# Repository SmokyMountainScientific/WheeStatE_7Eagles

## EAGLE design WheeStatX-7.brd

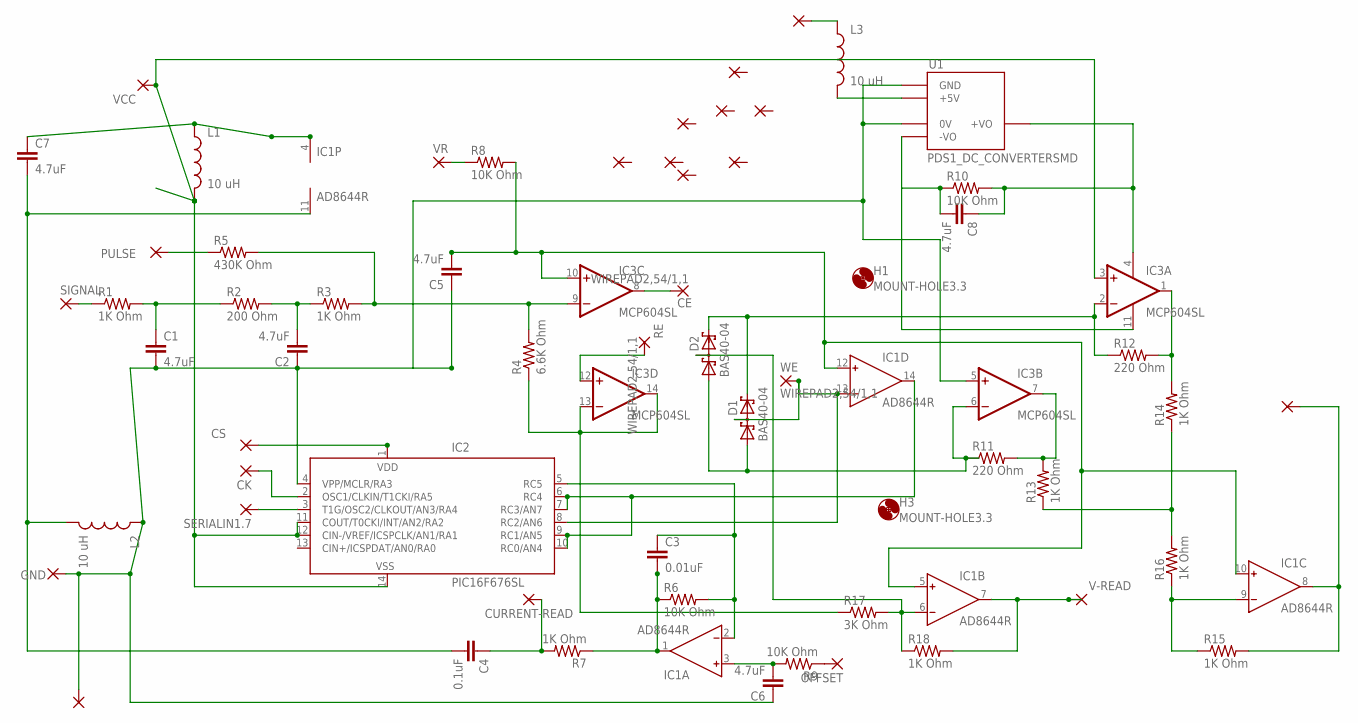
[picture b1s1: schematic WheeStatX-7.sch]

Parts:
1, 1.1, 1.4, 2, 3, 4, 5, 6, 7, 9, 10: 1,6/0,9
C1, C2, C5, C6, C8: 4.7uF; C0603
C3: 0.01uF; C0603
C4: 0.1uF; C0603
C7: 4.7uF; C0603@1
CE: WIREPAD2,54/1,1; 2,54/1,1
CK: 1,6/0,9
CS: 1,6/0,9
CURRENT-READ: 1,6/0,9
D1, D2: BAS40-04; SOT23
GND: 1,6/0,9
H1, H3: MOUNT-HOLE3.3; 3,3
IC1: AD8644R; SO14
IC2: PIC16F676SL; SO-14
IC3: MCP604SL; SO14
L1, L2, L3: 10 uH; 0603
OFFSET: 1,6/0,9
PULSE: 1,6/0,9
R1, R3, R7, R13, R14, R15, R16, R18: 1K Ohm; R0603
R2: 200 Ohm; R0603
R4: 6.6K Ohm; R0603
R5: 430K Ohm; R0603
R6, R8, R9, R10: 10K Ohm; R0603
R11, R12: 220 Ohm; R0603
R17: 3K Ohm; R0603
RE: WIREPAD2,54/1,1; 2,54/1,1
SERIALIN1.7: 1,6/0,9
SIGNAL: 1,6/0,9
U1: PDS1_DC_CONVERTERSMD; PDS1
V-READ: 1,6/0,9
VCC: 1,6/0,9
VR: 1,6/0,9
WE: WIREPAD2,54/1,1; 2,54/1,1

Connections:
GND: 1.1.1, C1.2, C2.1, C5.1, C6.1, GND.1, IC2.4 (VPP/MCLR/RA3), IC3.5 (+IN), L2.1, U1.1 (GND), U1.4 (0V)
unnamed: IC1.9 (IN-), R15.1, R16.1
unnamed: IC3.13 (-IN), IC3.14 (OUT), R4.1, R17.1
unnamed: IC3.12 (+IN), RE.1
unnamed: C4.1, CURRENT-READ.1, R7.2
unnamed: CE.1, IC3.8 (OUT)
unnamed: C3.2, IC1.1 (OUT), R6.1, R7.1
unnamed: C5.2, IC1.5 (IN+), IC1.10 (IN+), IC1.12 (IN+), IC3.10 (+IN), R8.2
unnamed: L3.2, U1.2 (+5V)
unnamed: R1.1, SIGNAL.1
unnamed: C4.2, C7.2, IC1.11 (V-), L2.2
unnamed: PULSE.1, R5.1
unnamed: C1.1, R1.2, R2.1
unnamed: CS.1, IC2.1 (VDD)
unnamed: C8.1, IC3.4 (V+), R10.2, U1.7 (+VO)
unnamed: D1.3 (C1A2), IC1.13 (IN-), IC2.8 (RC2/AN6), WE.1
unnamed: IC2.11 (COUT/T0CKI/INT/AN2/RA2), IC2.12 (CIN-/VREF/ICSPCLK/AN1/RA1), IC2.14 (VSS), IC3.3 (+IN), L1.2, VCC.1
unnamed: C2.2, R2.2, R3.1
unnamed: IC2.3 (T1G/OSC2/CLKOUT/AN3/RA4), SERIALIN1.7.1
unnamed: IC3.9 (-IN), R3.2, R4.2, R5.2
unnamed: D1.2 (C2), D2.2 (C2), IC3.2 (-IN), R12.1
unnamed: IC1.14 (OUT), IC2.6 (RC4), IC2.7 (RC3/AN7), IC2.9 (RC1/AN5), IC2.10 (RC0/AN4)
unnamed: CK.1, IC2.2 (OSC1/CLKIN/T1CKI/RA5)
unnamed: C8.2, IC3.11 (V-), R10.1, U1.5 (-VO)
unnamed: R13.1, R14.1, R16.2
unnamed: 9.1, L3.1
unnamed: D1.1 (A1), D2.1 (A1), IC3.6 (-IN), R11.1
unnamed: 1.4.1, IC1.8 (OUT), R15.2
unnamed: IC3.7 (OUT), R11.2, R13.2
unnamed: C6.2, IC1.3 (IN+), R9.2
unnamed: OFFSET.1, R9.1
unnamed: C3.1, IC1.2 (IN-), IC2.5 (RC5), R6.2
unnamed: D2.3 (C1A2), IC1.6 (IN-), R17.2, R18.1
unnamed: IC3.1 (OUT), R12.2, R14.2
unnamed: R8.1, VR.1
unnamed: C7.1, IC1.4 (V+), L1.1
unnamed: IC1.7 (OUT), R18.2, V-READ.1

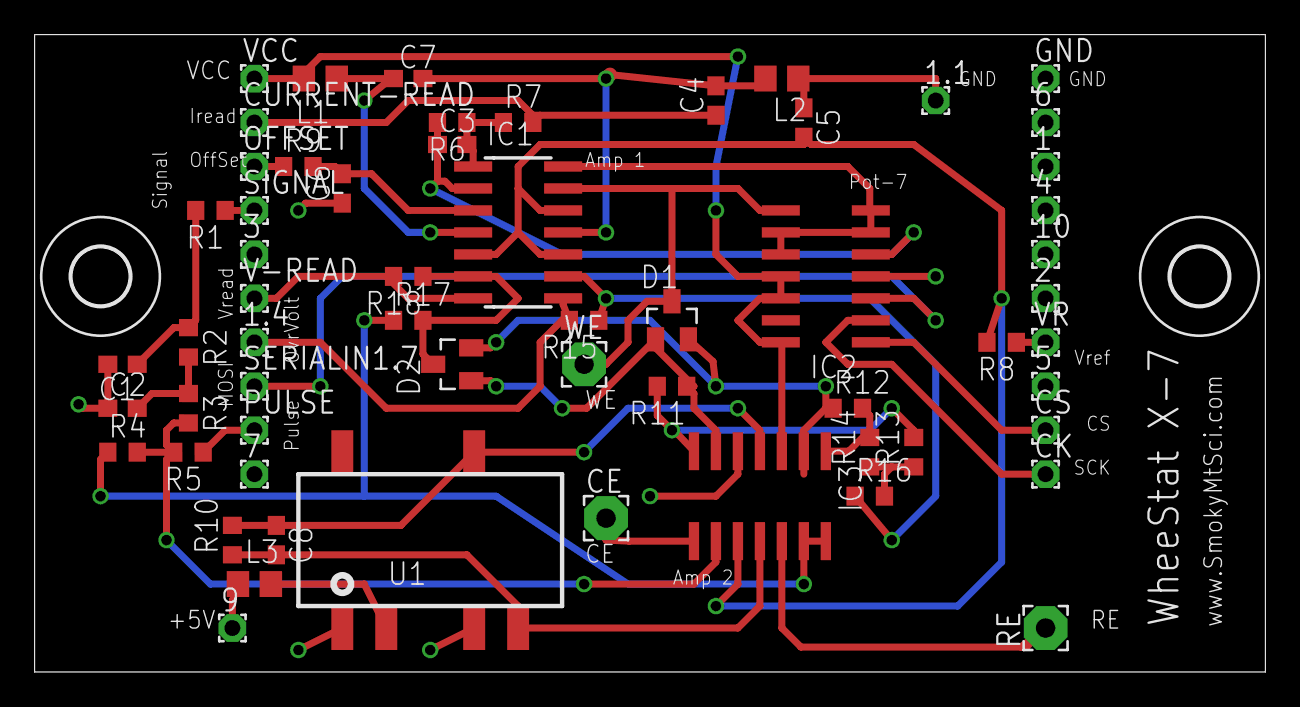
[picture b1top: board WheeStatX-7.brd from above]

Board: 2 copper layers, 71.1 x 36.8 mm, 62 parts (0 on the bottom side), 37 nets.

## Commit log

2015-10-21 :tada: Added .gitattributes & .gitignore files
2015-10-21 Eagle files for new generation WheeStat
    Analog board files for potentiostat with +/- 12 compliance voltage and
    +/- 5 volts range on working electrode

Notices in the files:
parts and their libraries:
SparkFun-Passives: Licensing: Creative Commons ShareAlike 4.0 International - https://creativecommons.org/licenses/by-sa/4.0
